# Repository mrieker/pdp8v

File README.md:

Vacuum tube implementation of PDP-8/V using a Raspberry PI for memory and I/O devices.
Webpage:  https://www.outerworldapps.com/pdp8v
Latest routed PCBs:
    https://www.outerworldapps.com/pdp8v/acl-2024-04-15.tgz
    https://www.outerworldapps.com/pdp8v/alu-2024-04-15.tgz
    https://www.outerworldapps.com/pdp8v/ma-2024-04-15.tgz
    https://www.outerworldapps.com/pdp8v/pc-2024-04-15.tgz
    https://www.outerworldapps.com/pdp8v/rpi-2024-04-15.tgz
    https://www.outerworldapps.com/pdp8v/seq-2024-04-15.tgz

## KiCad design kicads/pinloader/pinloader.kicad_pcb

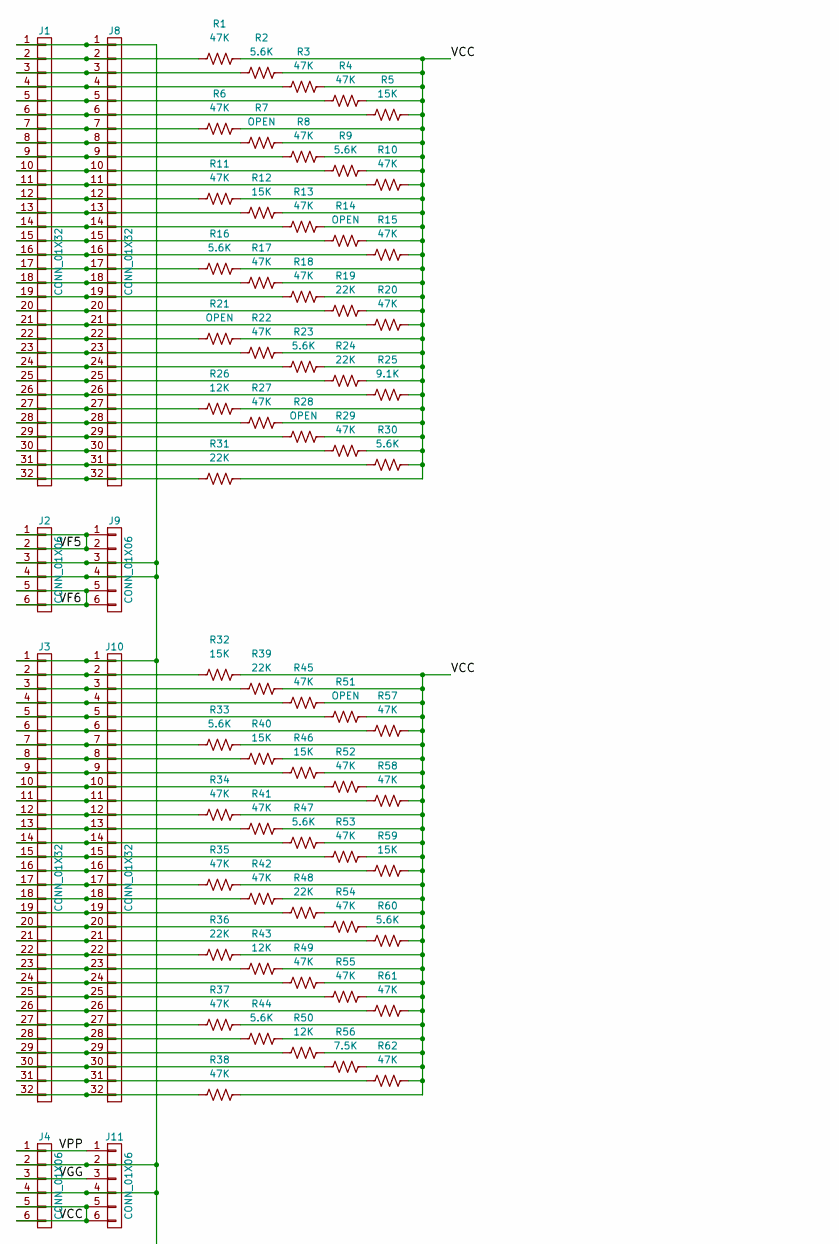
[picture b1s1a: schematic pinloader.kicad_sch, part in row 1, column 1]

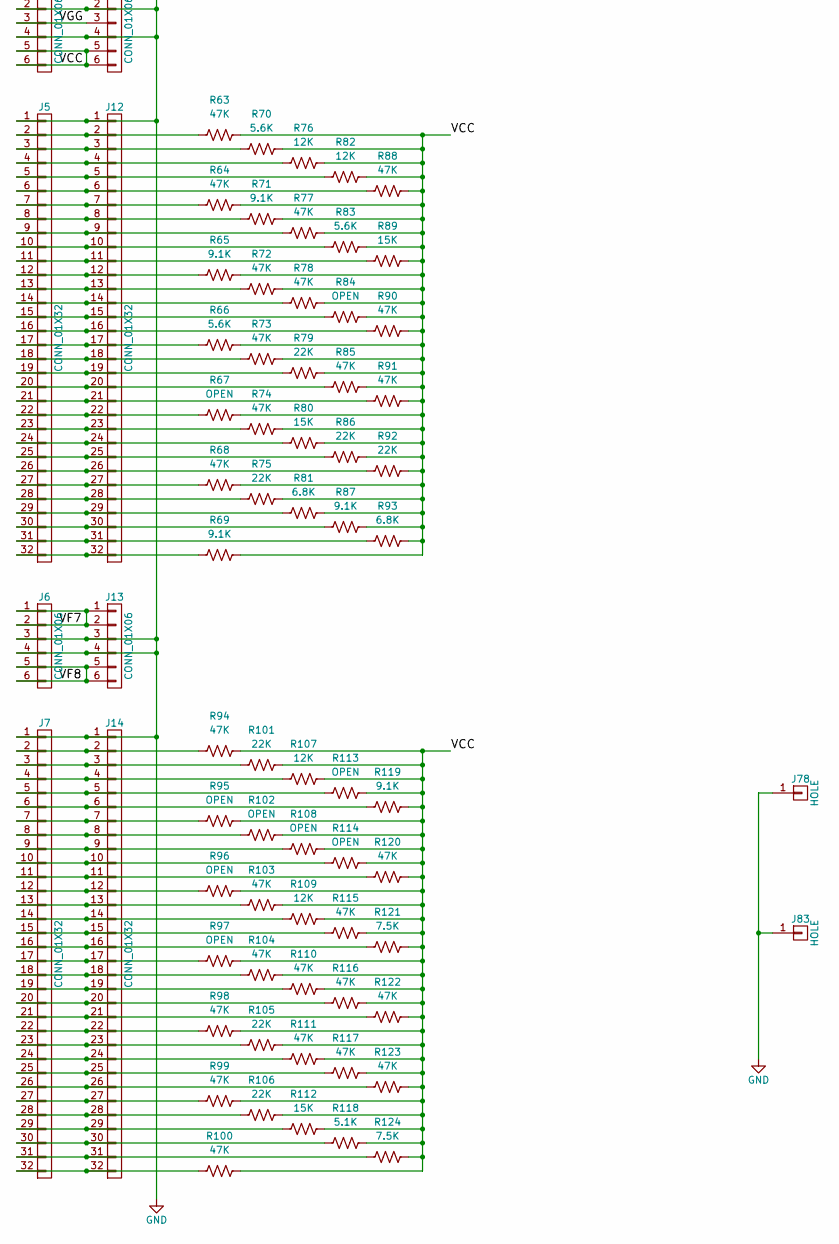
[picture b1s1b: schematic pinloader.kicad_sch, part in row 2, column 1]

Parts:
J1, J3, J5, J7, J8, J10, J12, J14: CONN_01X32; Pin_Header_Straight_1x32_Pitch2.54mm
J2, J4, J6, J9, J11, J13: CONN_01X06; Pin_Header_Straight_1x06_Pitch2.54mm
J78, J83: HOLE; 1pin
R1, R3, R4, R6, R8, R10, R11, R13, R15, R17, R18, R20, R22, R27, R29, R34, R35, R37, R38, R41, R42, R45, R49, R52, R53, R54, R55, R57, R58, R61, R62, R63, R64, R68, R72, R73, R74, R77, R78, R85, R88, R90, R91, R94, R98, R99, R100, R103, R104, R110, R111, R115, R116, R117, R120, R122, R123: 47K; R_Axial_DIN0207_L6.3mm_D2.5mm_P10.16mm_Horizontal
R2, R9, R16, R23, R30, R33, R44, R47, R60, R66, R70, R83: 5.6K; R_Axial_DIN0207_L6.3mm_D2.5mm_P10.16mm_Horizontal
R5, R12, R32, R40, R46, R59, R80, R89, R112: 15K; R_Axial_DIN0207_L6.3mm_D2.5mm_P10.16mm_Horizontal
R7, R14, R21, R28, R51, R67, R84, R95, R96, R97, R102, R108, R113, R114: OPEN; R_Axial_DIN0207_L6.3mm_D2.5mm_P10.16mm_Horizontal
R19, R24, R31, R36, R39, R48, R75, R79, R86, R92, R101, R105, R106: 22K; R_Axial_DIN0207_L6.3mm_D2.5mm_P10.16mm_Horizontal
R25, R65, R69, R71, R87, R119: 9.1K; R_Axial_DIN0207_L6.3mm_D2.5mm_P10.16mm_Horizontal
R26, R43, R50, R76, R82, R107, R109: 12K; R_Axial_DIN0207_L6.3mm_D2.5mm_P10.16mm_Horizontal
R56, R121, R124: 7.5K; R_Axial_DIN0207_L6.3mm_D2.5mm_P10.16mm_Horizontal
R81, R93: 6.8K; R_Axial_DIN0207_L6.3mm_D2.5mm_P10.16mm_Horizontal
R118: 5.1K; R_Axial_DIN0207_L6.3mm_D2.5mm_P10.16mm_Horizontal

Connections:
/VCC: J4.5, J4.6, J11.5, J11.6, R1.2, R2.2, R3.2, R4.2, R5.2, R6.2, R7.2, R8.2, R9.2, R10.2, R11.2, R12.2, R13.2, R14.2, R15.2, R16.2, R17.2, R18.2, R19.2, R20.2, R21.2, R22.2, R23.2, R24.2, R25.2, R26.2, R27.2, R28.2, R29.2, R30.2, R31.2, R32.2, R33.2, R34.2, R35.2, R36.2, R37.2, R38.2, R39.2, R40.2, R41.2, R42.2, R43.2, R44.2, R45.2, R46.2, R47.2, R48.2, R49.2, R50.2, R51.2, R52.2, R53.2, R54.2, R55.2, R56.2, R57.2, R58.2, R59.2, R60.2, R61.2, R62.2, R63.2, R64.2, R65.2, R66.2, R67.2, R68.2, R69.2, R70.2, R71.2, R72.2, R73.2, R74.2, R75.2, R76.2, R77.2, R78.2, R79.2, R80.2, R81.2, R82.2, R83.2, R84.2, R85.2, R86.2, R87.2, R88.2, R89.2, R90.2, R91.2, R92.2, R93.2, R94.2, R95.2, R96.2, R97.2, R98.2, R99.2, R100.2, R101.2, R102.2, R103.2, R104.2, R105.2, R106.2, R107.2, R108.2, R109.2, R110.2, R111.2, R112.2, R113.2, R114.2, R115.2, R116.2, R117.2, R118.2, R119.2, R120.2, R121.2, R122.2, R123.2, R124.2
/VF5: J2.1, J2.2, J9.1, J9.2
/VF6: J2.5, J2.6, J9.5, J9.6
/VF7: J6.1, J6.2, J13.1, J13.2
/VF8: J6.5, J6.6, J13.5, J13.6
/VGG: J4.3, J11.3
/VPP: J4.1, J11.1
GND: J1.1, J2.3, J2.4, J3.1, J4.2, J4.4, J5.1, J6.3, J6.4, J7.1, J8.1, J9.3, J9.4, J10.1, J11.2, J11.4, J12.1, J13.3, J13.4, J14.1, J78.1, J83.1
unnamed: J1.2, J8.2, R1.1
unnamed: J1.3, J8.3, R2.1
unnamed: J1.4, J8.4, R3.1
unnamed: J1.5, J8.5, R4.1
unnamed: J1.6, J8.6, R5.1
unnamed: J1.7, J8.7, R6.1
unnamed: J1.8, J8.8, R7.1
unnamed: J1.9, J8.9, R8.1
unnamed: J1.10, J8.10, R9.1
unnamed: J1.11, J8.11, R10.1
unnamed: J1.12, J8.12, R11.1
unnamed: J1.13, J8.13, R12.1
unnamed: J1.14, J8.14, R13.1
unnamed: J1.15, J8.15, R14.1
unnamed: J1.16, J8.16, R15.1
unnamed: J1.17, J8.17, R16.1
unnamed: J1.18, J8.18, R17.1
unnamed: J1.19, J8.19, R18.1
unnamed: J1.20, J8.20, R19.1
unnamed: J1.21, J8.21, R20.1
unnamed: J1.22, J8.22, R21.1
unnamed: J1.23, J8.23, R22.1
unnamed: J1.24, J8.24, R23.1
unnamed: J1.25, J8.25, R24.1
unnamed: J1.26, J8.26, R25.1
unnamed: J1.27, J8.27, R26.1
unnamed: J1.28, J8.28, R27.1
unnamed: J1.29, J8.29, R28.1
unnamed: J1.30, J8.30, R29.1
unnamed: J1.31, J8.31, R30.1
unnamed: J1.32, J8.32, R31.1
unnamed: J3.2, J10.2, R32.1
unnamed: J3.3, J10.3, R39.1
unnamed: J3.4, J10.4, R45.1
unnamed: J3.5, J10.5, R51.1
unnamed: J3.6, J10.6, R57.1
unnamed: J3.7, J10.7, R33.1
unnamed: J3.8, J10.8, R40.1
unnamed: J3.9, J10.9, R46.1
unnamed: J3.10, J10.10, R52.1
unnamed: J3.11, J10.11, R58.1
unnamed: J3.12, J10.12, R34.1
unnamed: J3.13, J10.13, R41.1
unnamed: J3.14, J10.14, R47.1
unnamed: J3.15, J10.15, R53.1
unnamed: J3.16, J10.16, R59.1
unnamed: J3.17, J10.17, R35.1
unnamed: J3.18, J10.18, R42.1
unnamed: J3.19, J10.19, R48.1
unnamed: J3.20, J10.20, R54.1
unnamed: J3.21, J10.21, R60.1
unnamed: J3.22, J10.22, R36.1
unnamed: J3.23, J10.23, R43.1
unnamed: J3.24, J10.24, R49.1
unnamed: J3.25, J10.25, R55.1
unnamed: J3.26, J10.26, R61.1
unnamed: J3.27, J10.27, R37.1
unnamed: J3.28, J10.28, R44.1
unnamed: J3.29, J10.29, R50.1
unnamed: J3.30, J10.30, R56.1
unnamed: J3.31, J10.31, R62.1
unnamed: J3.32, J10.32, R38.1
unnamed: J5.2, J12.2, R63.1
unnamed: J5.3, J12.3, R70.1
unnamed: J5.4, J12.4, R76.1
unnamed: J5.5, J12.5, R82.1
unnamed: J5.6, J12.6, R88.1
unnamed: J5.7, J12.7, R64.1
unnamed: J5.8, J12.8, R71.1
unnamed: J5.9, J12.9, R77.1
unnamed: J5.10, J12.10, R83.1
unnamed: J5.11, J12.11, R89.1
unnamed: J5.12, J12.12, R65.1
unnamed: J5.13, J12.13, R72.1
unnamed: J5.14, J12.14, R78.1
unnamed: J5.15, J12.15, R84.1
unnamed: J5.16, J12.16, R90.1
unnamed: J5.17, J12.17, R66.1
unnamed: J5.18, J12.18, R73.1
unnamed: J5.19, J12.19, R79.1
unnamed: J5.20, J12.20, R85.1
unnamed: J5.21, J12.21, R91.1
unnamed: J5.22, J12.22, R67.1
unnamed: J5.23, J12.23, R74.1
unnamed: J5.24, J12.24, R80.1
unnamed: J5.25, J12.25, R86.1
unnamed: J5.26, J12.26, R92.1
unnamed: J5.27, J12.27, R68.1
unnamed: J5.28, J12.28, R75.1
unnamed: J5.29, J12.29, R81.1
unnamed: J5.30, J12.30, R87.1
unnamed: J5.31, J12.31, R93.1
unnamed: J5.32, J12.32, R69.1
unnamed: J7.2, J14.2, R94.1
unnamed: J7.3, J14.3, R101.1
unnamed: J7.4, J14.4, R107.1
unnamed: J7.5, J14.5, R113.1
unnamed: J7.6, J14.6, R119.1
unnamed: J7.7, J14.7, R95.1
unnamed: J7.8, J14.8, R102.1
unnamed: J7.9, J14.9, R108.1
unnamed: J7.10, J14.10, R114.1
unnamed: J7.11, J14.11, R120.1
unnamed: J7.12, J14.12, R96.1
unnamed: J7.13, J14.13, R103.1
unnamed: J7.14, J14.14, R109.1
unnamed: J7.15, J14.15, R115.1
unnamed: J7.16, J14.16, R121.1
unnamed: J7.17, J14.17, R97.1
unnamed: J7.18, J14.18, R104.1
unnamed: J7.19, J14.19, R110.1
unnamed: J7.20, J14.20, R116.1
unnamed: J7.21, J14.21, R122.1
unnamed: J7.22, J14.22, R98.1
unnamed: J7.23, J14.23, R105.1
unnamed: J7.24, J14.24, R111.1
unnamed: J7.25, J14.25, R117.1
unnamed: J7.26, J14.26, R123.1
unnamed: J7.27, J14.27, R99.1
unnamed: J7.28, J14.28, R106.1
unnamed: J7.29, J14.29, R112.1
unnamed: J7.30, J14.30, R118.1
unnamed: J7.31, J14.31, R124.1
unnamed: J7.32, J14.32, R100.1

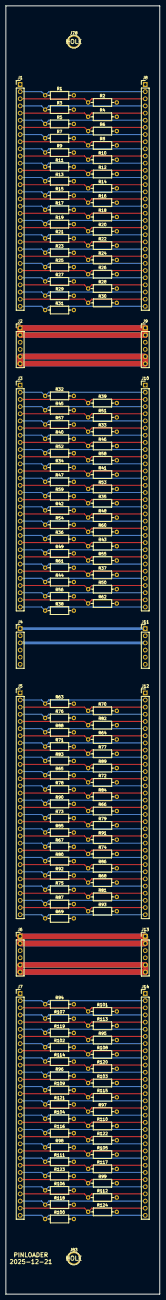
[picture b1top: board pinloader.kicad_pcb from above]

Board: 4 copper layers, 54.6 x 457.2 mm, 140 parts (0 on the bottom side), 132 nets.

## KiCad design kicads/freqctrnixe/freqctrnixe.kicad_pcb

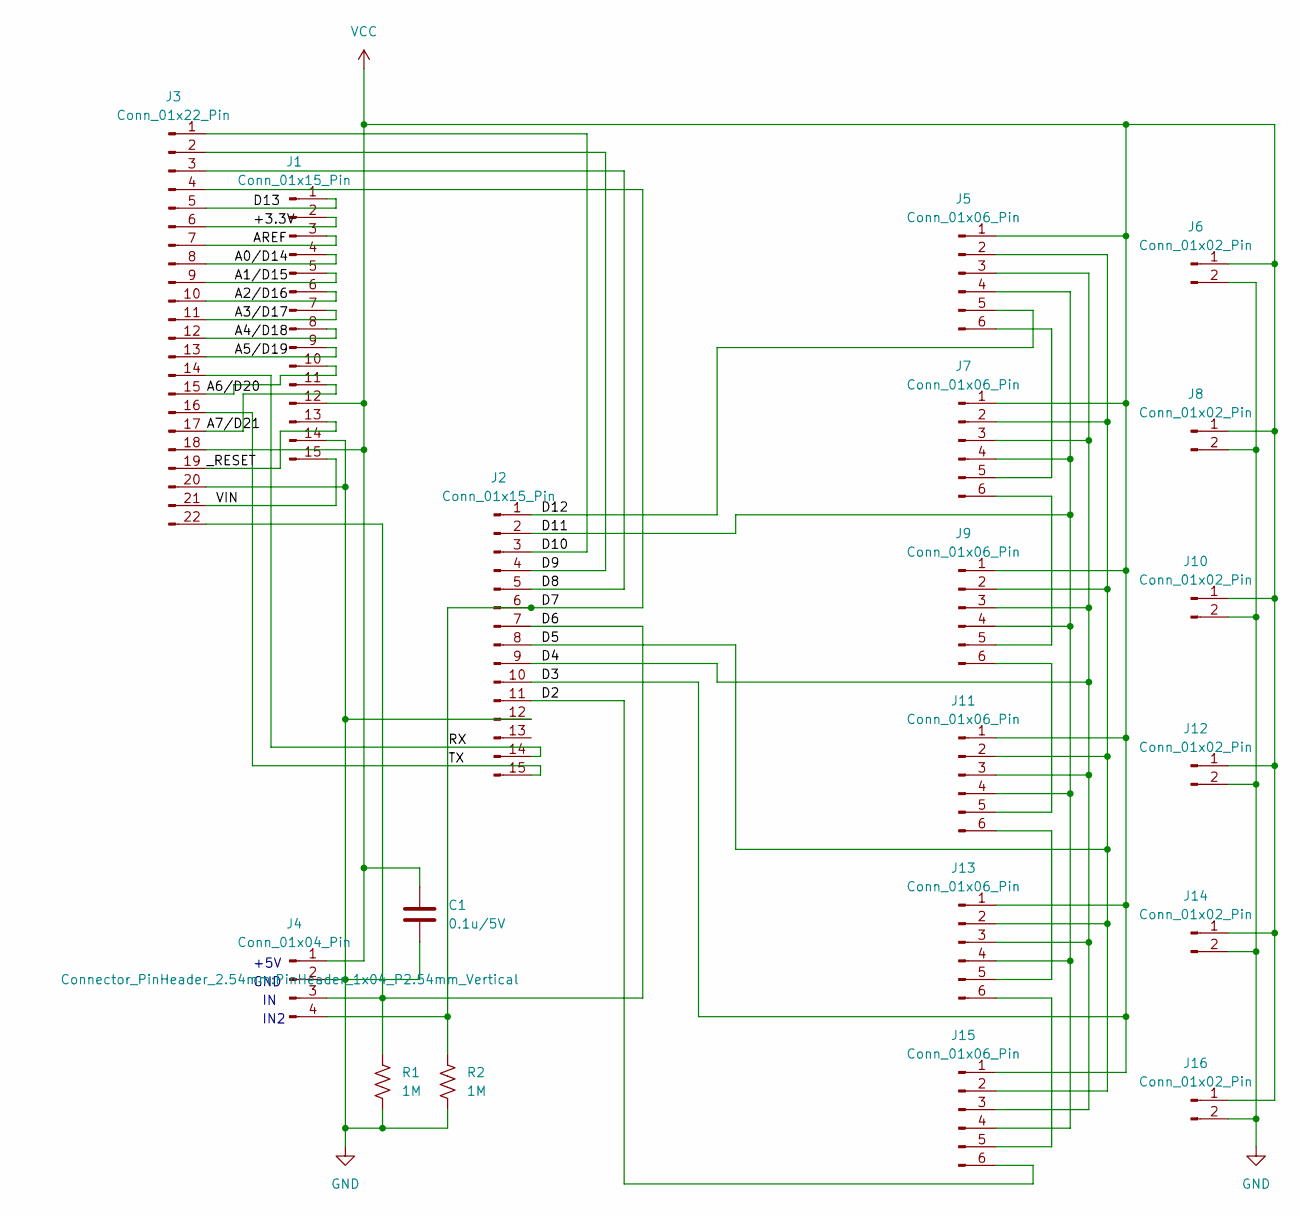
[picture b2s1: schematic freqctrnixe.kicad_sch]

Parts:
C1: 0.1u/5V; C_Axial_L3.8mm_D2.6mm_P7.50mm_Horizontal
J1, J2: Conn_01x15_Pin; PinHeader_1x15_P2.54mm_Vertical
J3: Conn_01x22_Pin; PinHeader_1x22_P2.54mm_Vertical
J4: Conn_01x04_Pin; PinHeader_1x04_P2.54mm_Vertical
J5, J7, J9, J11, J13, J15: Conn_01x06_Pin; PinHeader_1x06_P2.54mm_Vertical
J6, J8, J10, J12, J14, J16: Conn_01x02_Pin; PinHeader_1x02_P2.54mm_Vertical
R1, R2: 1M; R_Axial_DIN0204_L3.6mm_D1.6mm_P7.62mm_Horizontal

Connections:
/+3.3V: J1.2, J3.6
/A0/D14: J1.4, J3.8
/A1/D15: J1.5, J3.9
/A2/D16: J1.6, J3.10
/A3/D17: J1.7, J3.11
/A4/D18: J1.8, J3.12
/A5/D19: J1.9, J3.13
/A6/D20: J1.10, J3.15
/A7/D21: J1.11, J3.17
/AREF: J1.3, J3.7
/D2: J2.11, J15.6
/D4: J2.9, J5.3, J7.3, J9.3, J11.3, J13.3, J15.3
/D5: J2.8, J5.2, J7.2, J9.2, J11.2, J13.2, J15.2
/D6: J2.7, J3.22, J4.3, R1.1
/D8: J2.5, J3.3
/D9: J2.4, J3.2
/D10: J2.3, J3.1
/D11: J2.2, J5.4, J7.4, J9.4, J11.4, J13.4, J15.4
/D12: J2.1, J5.5
/D13: J1.1, J3.5
/VIN: J1.15, J3.21
/_RESET: J1.13, J3.19
GND: C1.2, J1.14, J2.12, J3.20, J4.2, J6.2, J8.2, J10.2, J12.2, J14.2, J16.2, R1.2, R2.2
unnamed: J5.6, J7.5
unnamed: J7.6, J9.5
unnamed: J9.6, J11.5
unnamed: J11.6, J13.5
unnamed: J13.6, J15.5
VCC: C1.1, J1.12, J2.10, J3.18, J4.1, J5.1, J6.1, J7.1, J8.1, J9.1, J10.1, J11.1, J12.1, J13.1, J14.1, J15.1, J16.1

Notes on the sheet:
+5V
IN2
GND

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
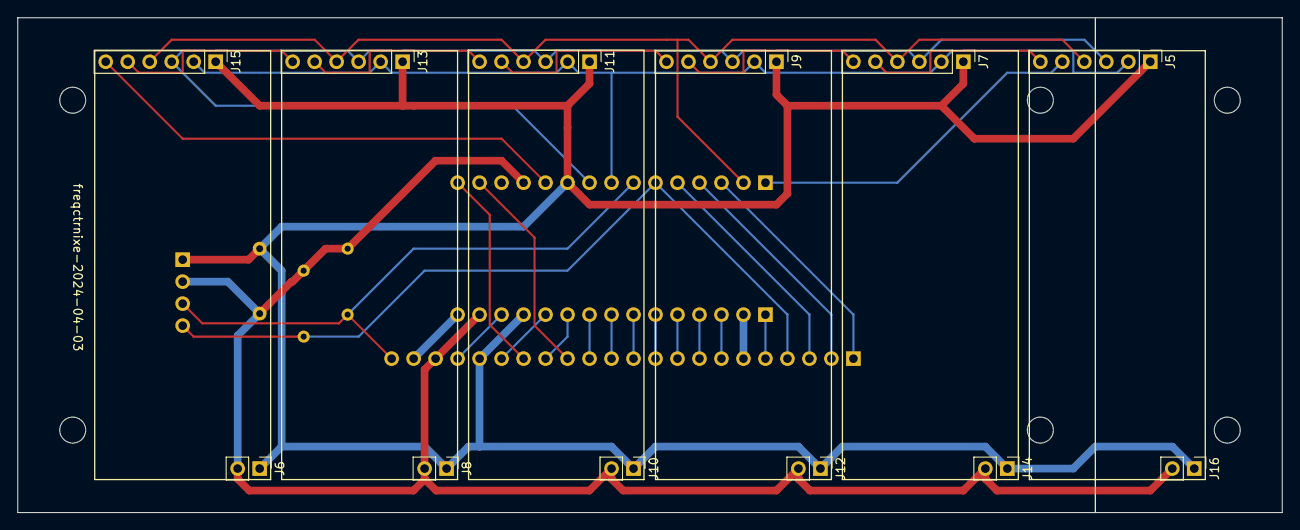
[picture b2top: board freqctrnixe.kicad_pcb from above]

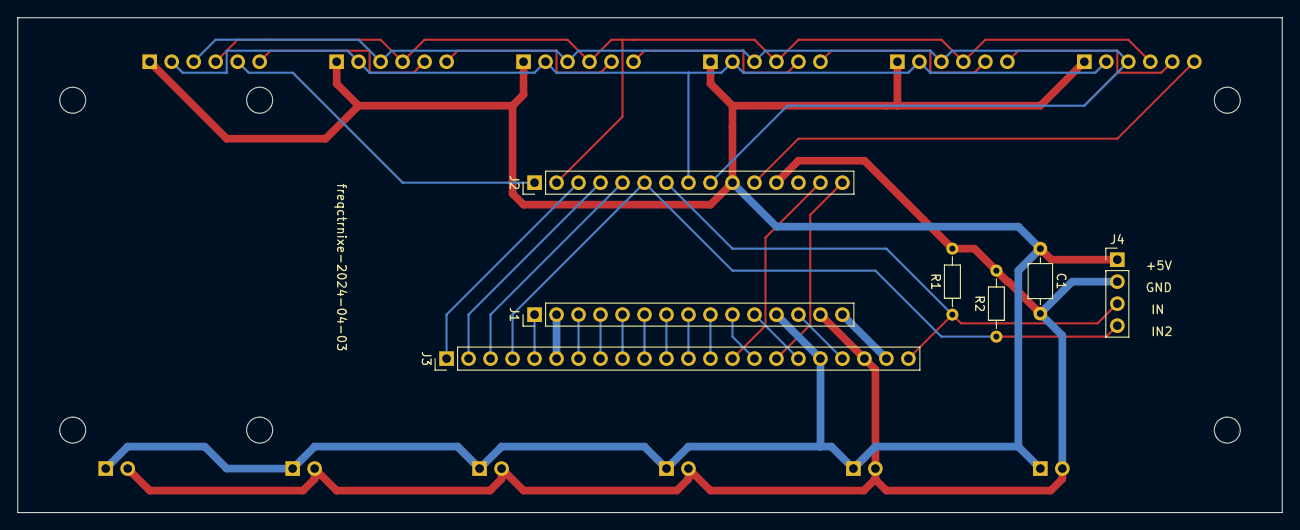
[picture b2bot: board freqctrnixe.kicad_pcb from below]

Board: 2 copper layers, 146.1 x 57.1 mm, 19 parts (7 on the bottom side), 32 nets.

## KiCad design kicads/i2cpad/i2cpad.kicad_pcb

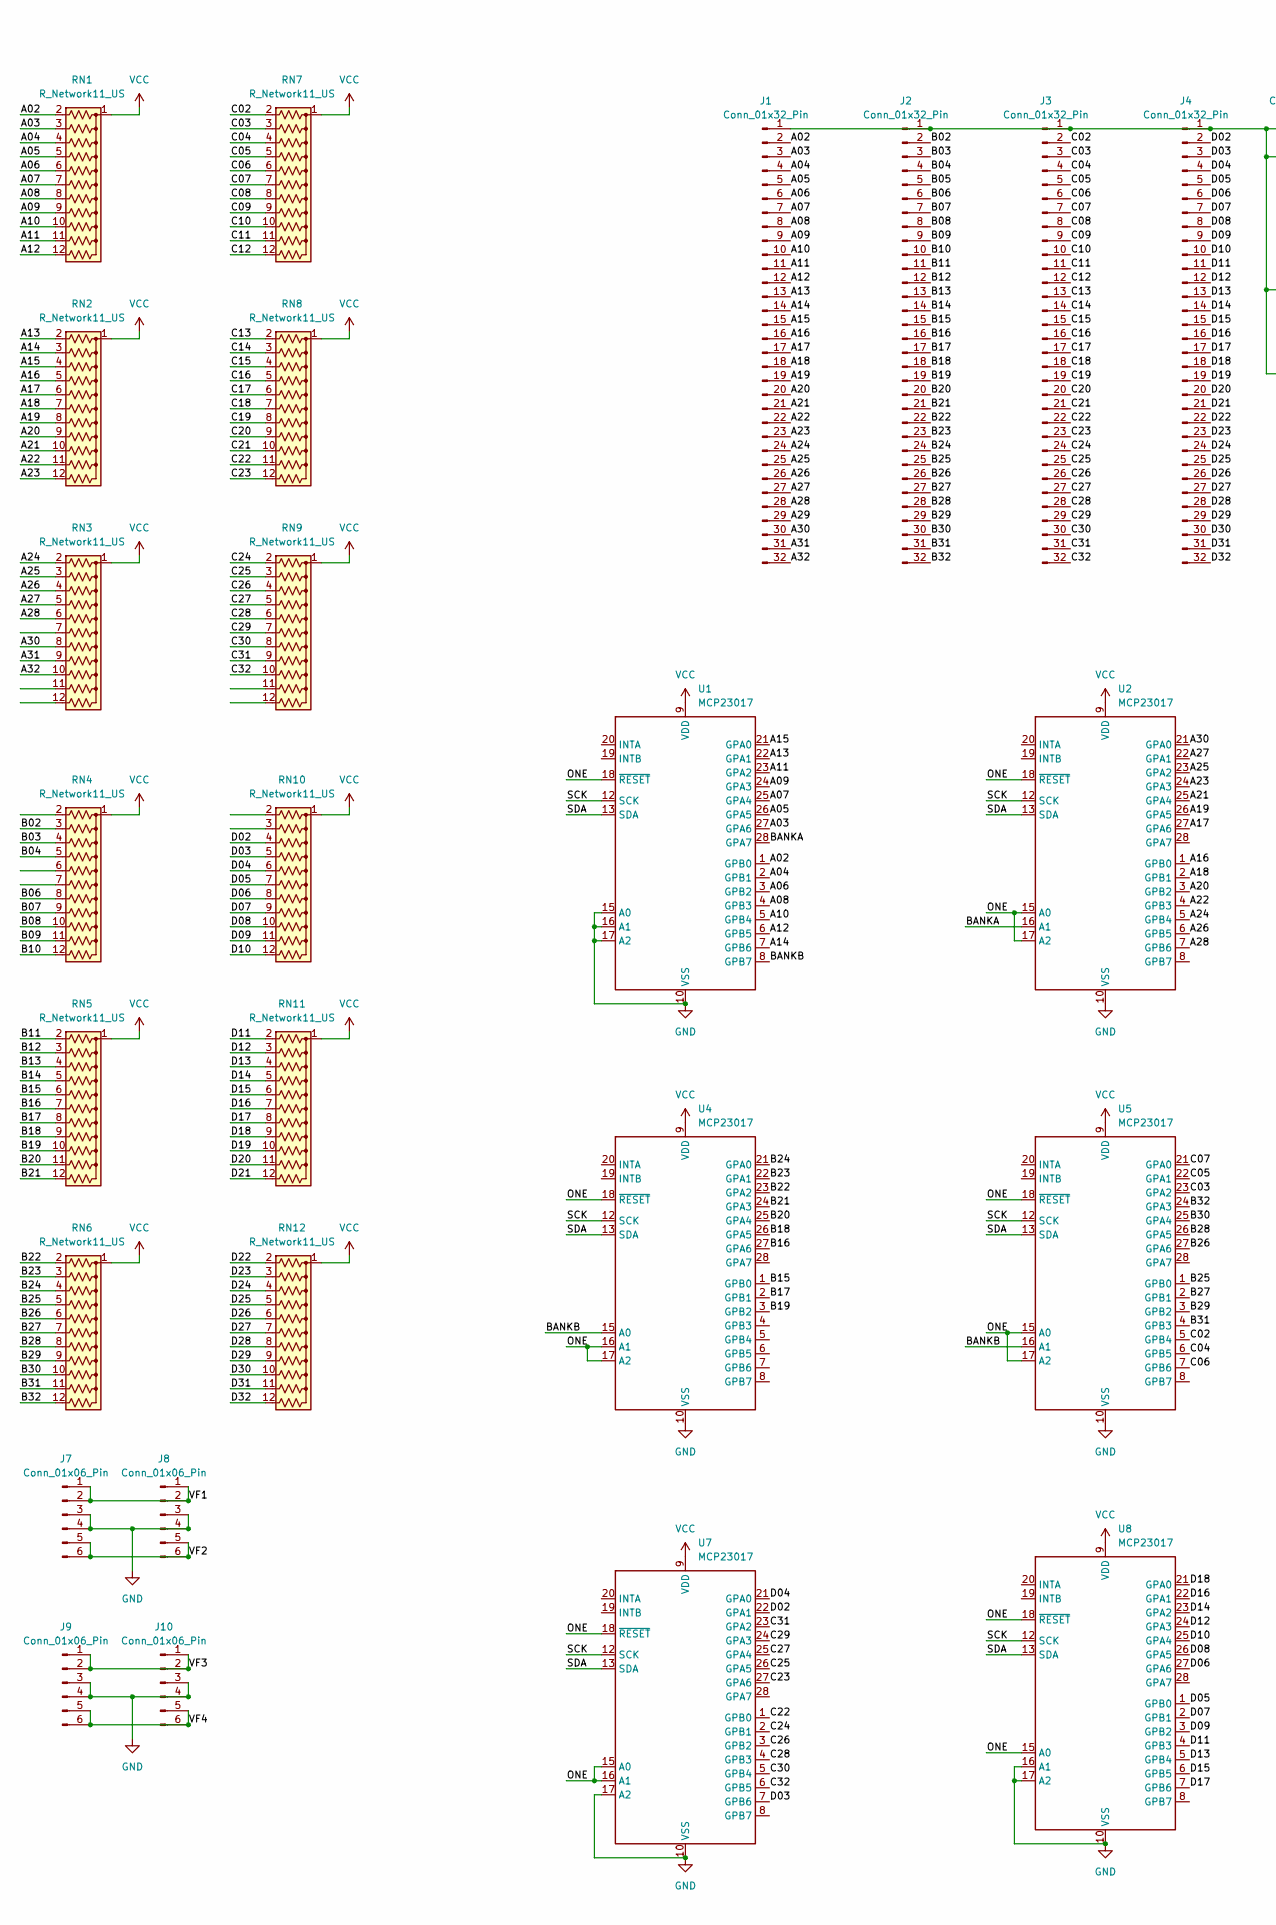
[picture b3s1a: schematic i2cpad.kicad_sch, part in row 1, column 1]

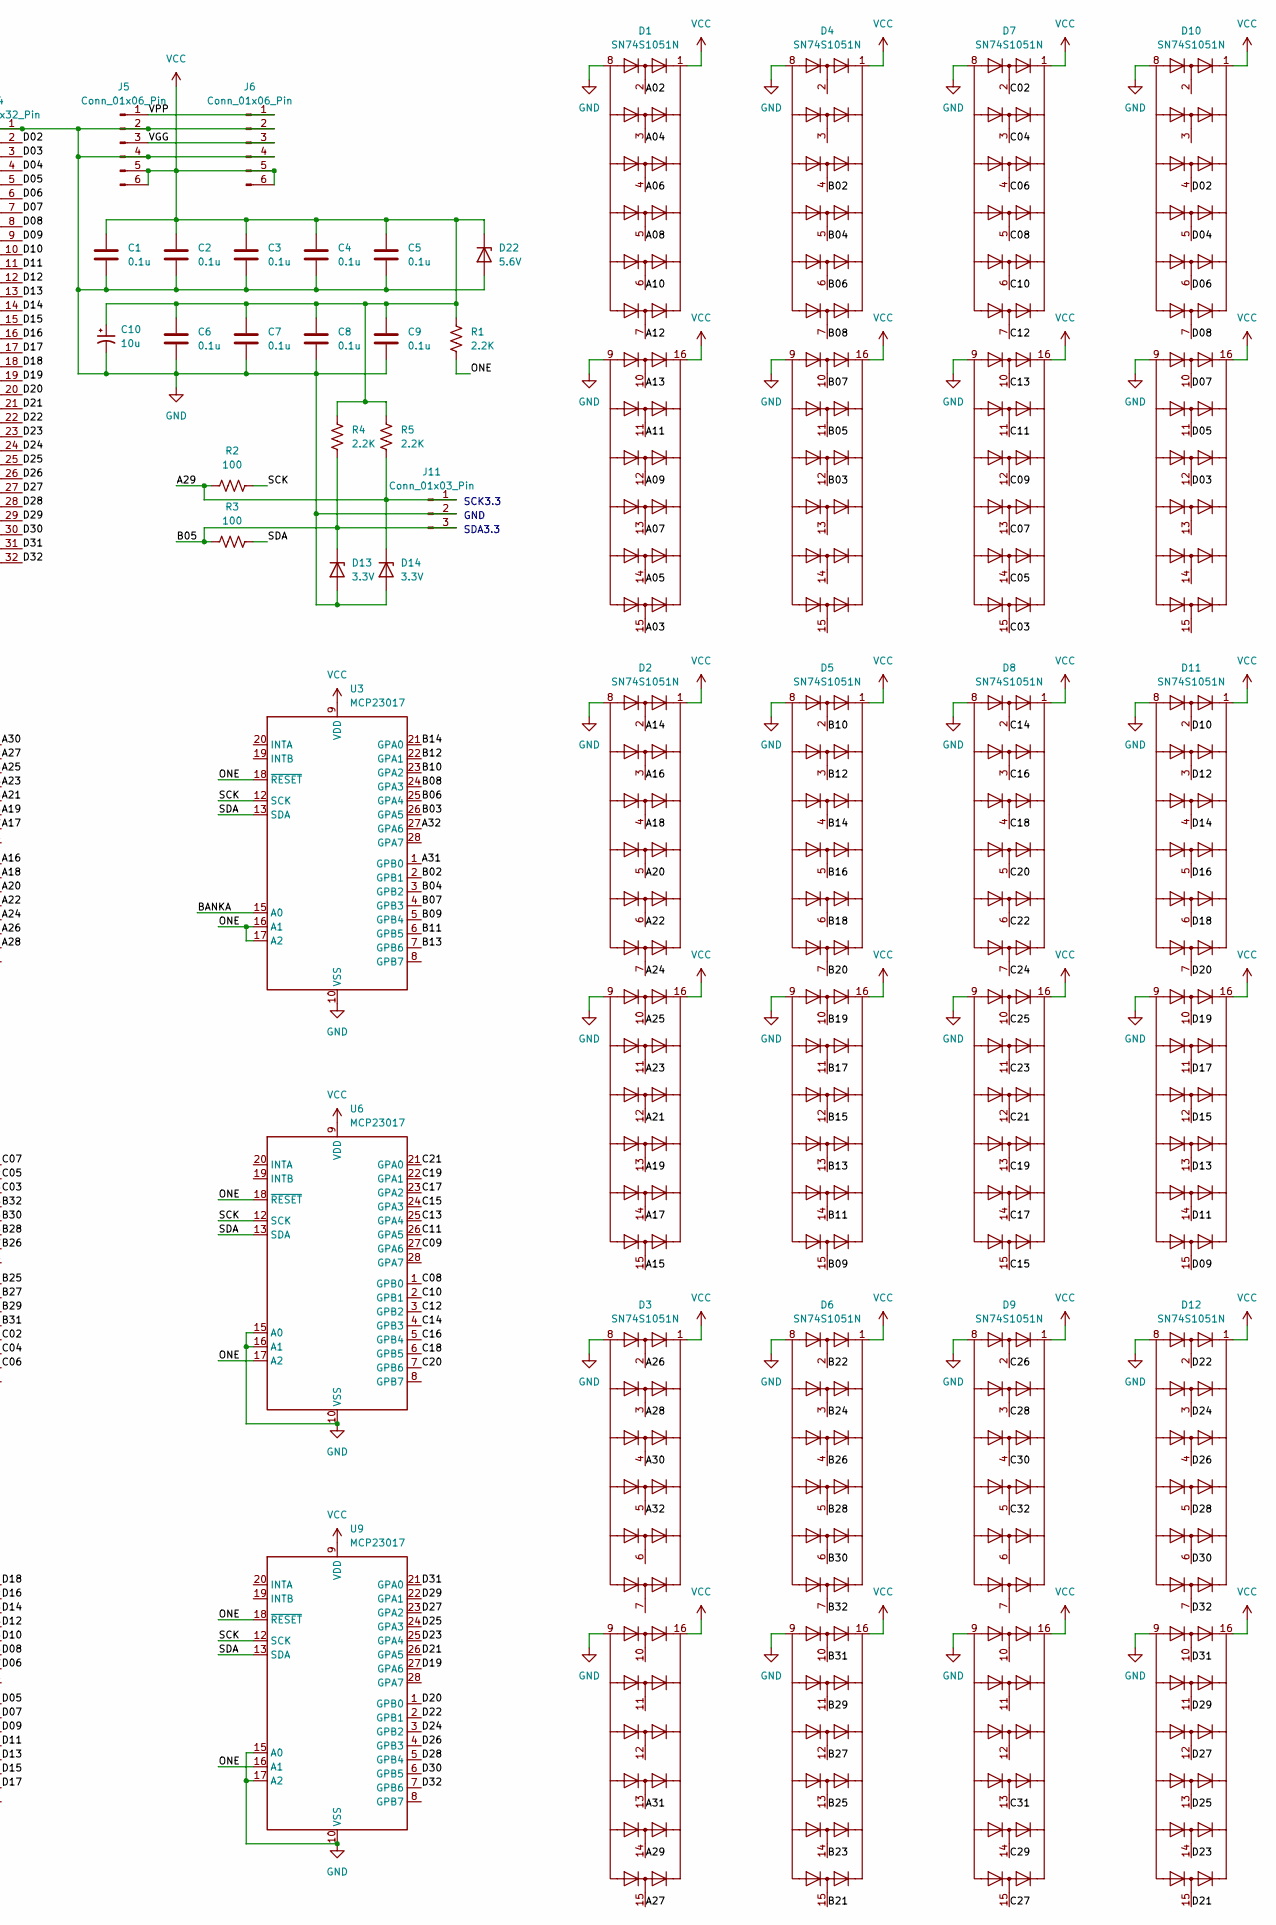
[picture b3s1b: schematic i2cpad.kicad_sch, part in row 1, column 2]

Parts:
C1, C2, C3, C4, C5, C6, C7, C8, C9: 0.1u; C_Axial_L5.1mm_D3.1mm_P7.50mm_Horizontal
C10: 10u; CP_Axial_L10.0mm_D4.5mm_P15.00mm_Horizontal
D1, D2, D3, D4, D5, D6, D7, D8, D9, D10, D11, D12: SN74S1051N; DIP-16_W7.62mm_LongPads
D13, D14: 3.3V; D_T-1_P10.16mm_Horizontal
D22: 5.6V; D_T-1_P10.16mm_Horizontal
J1, J2, J3, J4: Conn_01x32_Pin; PinHeader_1x32_P2.54mm_Vertical
J5, J6, J7, J8, J9, J10: Conn_01x06_Pin; PinHeader_1x06_P2.54mm_Vertical
J11: Conn_01x03_Pin; PinHeader_1x03_P2.54mm_Vertical
R1, R4, R5: 2.2K; R_Axial_DIN0204_L3.6mm_D1.6mm_P7.62mm_Horizontal
R2, R3: 100; R_Axial_DIN0204_L3.6mm_D1.6mm_P7.62mm_Horizontal
RN1, RN2, RN3, RN4, RN5, RN6, RN7, RN8, RN9, RN10, RN11, RN12: R_Network11_US; R_Array_SIP12
U1, U2, U3, U4, U5, U6, U7, U8, U9: MCP23017; DIP-28_W7.62mm_LongPads

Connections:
/A02: D1.2 (X2), J1.2, RN1.2 (R1), U1.1 (GPB0)
/A03: D1.15 (X15), J1.3, RN1.3 (R2), U1.27 (GPA6)
/A04: D1.3 (X3), J1.4, RN1.4 (R3), U1.2 (GPB1)
/A05: D1.14 (X14), J1.5, RN1.5 (R4), U1.26 (GPA5)
/A06: D1.4 (X4), J1.6, RN1.6 (R5), U1.3 (GPB2)
/A07: D1.13 (X13), J1.7, RN1.7 (R6), U1.25 (GPA4)
/A08: D1.5 (X5), J1.8, RN1.8 (R7), U1.4 (GPB3)
/A09: D1.12 (X12), J1.9, RN1.9 (R8), U1.24 (GPA3)
/A10: D1.6 (X6), J1.10, RN1.10 (R9), U1.5 (GPB4)
/A11: D1.11 (X11), J1.11, RN1.11 (R10), U1.23 (GPA2)
/A12: D1.7 (X7), J1.12, RN1.12 (R11), U1.6 (GPB5)
/A13: D1.10 (X10), J1.13, RN2.2 (R1), U1.22 (GPA1)
/A14: D2.2 (X2), J1.14, RN2.3 (R2), U1.7 (GPB6)
/A15: D2.15 (X15), J1.15, RN2.4 (R3), U1.21 (GPA0)
/A16: D2.3 (X3), J1.16, RN2.5 (R4), U2.1 (GPB0)
/A17: D2.14 (X14), J1.17, RN2.6 (R5), U2.27 (GPA6)
/A18: D2.4 (X4), J1.18, RN2.7 (R6), U2.2 (GPB1)
/A19: D2.13 (X13), J1.19, RN2.8 (R7), U2.26 (GPA5)
/A20: D2.5 (X5), J1.20, RN2.9 (R8), U2.3 (GPB2)
/A21: D2.12 (X12), J1.21, RN2.10 (R9), U2.25 (GPA4)
/A22: D2.6 (X6), J1.22, RN2.11 (R10), U2.4 (GPB3)
/A23: D2.11 (X11), J1.23, RN2.12 (R11), U2.24 (GPA3)
/A24: D2.7 (X7), J1.24, RN3.2 (R1), U2.5 (GPB4)
/A25: D2.10 (X10), J1.25, RN3.3 (R2), U2.23 (GPA2)
/A26: D3.2 (X2), J1.26, RN3.4 (R3), U2.6 (GPB5)
/A27: D3.15 (X15), J1.27, RN3.5 (R4), U2.22 (GPA1)
/A28: D3.3 (X3), J1.28, RN3.6 (R5), U2.7 (GPB6)
/A29: D3.14 (X14), D14.1 (K), J1.29, J11.1, R2.1, R5.2
/A30: D3.4 (X4), J1.30, RN3.8 (R7), U2.21 (GPA0)
/A31: D3.13 (X13), J1.31, RN3.9 (R8), U3.1 (GPB0)
/A32: D3.5 (X5), J1.32, RN3.10 (R9), U3.27 (GPA6)
/B02: D4.4 (X4), J2.2, RN4.3 (R2), U3.2 (GPB1)
/B03: D4.12 (X12), J2.3, RN4.4 (R3), U3.26 (GPA5)
/B04: D4.5 (X5), J2.4, RN4.5 (R4), U3.3 (GPB2)
/B05: D4.11 (X11), D13.1 (K), J2.5, J11.3, R3.1, R4.2
/B06: D4.6 (X6), J2.6, RN4.8 (R7), U3.25 (GPA4)
/B07: D4.10 (X10), J2.7, RN4.9 (R8), U3.4 (GPB3)
/B08: D4.7 (X7), J2.8, RN4.10 (R9), U3.24 (GPA3)
/B09: D5.15 (X15), J2.9, RN4.11 (R10), U3.5 (GPB4)
/B10: D5.2 (X2), J2.10, RN4.12 (R11), U3.23 (GPA2)
/B11: D5.14 (X14), J2.11, RN5.2 (R1), U3.6 (GPB5)
/B12: D5.3 (X3), J2.12, RN5.3 (R2), U3.22 (GPA1)
/B13: D5.13 (X13), J2.13, RN5.4 (R3), U3.7 (GPB6)
/B14: D5.4 (X4), J2.14, RN5.5 (R4), U3.21 (GPA0)
/B15: D5.12 (X12), J2.15, RN5.6 (R5), U4.1 (GPB0)
/B16: D5.5 (X5), J2.16, RN5.7 (R6), U4.27 (GPA6)
/B17: D5.11 (X11), J2.17, RN5.8 (R7), U4.2 (GPB1)
/B18: D5.6 (X6), J2.18, RN5.9 (R8), U4.26 (GPA5)
/B19: D5.10 (X10), J2.19, RN5.10 (R9), U4.3 (GPB2)
/B20: D5.7 (X7), J2.20, RN5.11 (R10), U4.25 (GPA4)
/B21: D6.15 (X15), J2.21, RN5.12 (R11), U4.24 (GPA3)
/B22: D6.2 (X2), J2.22, RN6.2 (R1), U4.23 (GPA2)
/B23: D6.14 (X14), J2.23, RN6.3 (R2), U4.22 (GPA1)
/B24: D6.3 (X3), J2.24, RN6.4 (R3), U4.21 (GPA0)
/B25: D6.13 (X13), J2.25, RN6.5 (R4), U5.1 (GPB0)
/B26: D6.4 (X4), J2.26, RN6.6 (R5), U5.27 (GPA6)
/B27: D6.12 (X12), J2.27, RN6.7 (R6), U5.2 (GPB1)
/B28: D6.5 (X5), J2.28, RN6.8 (R7), U5.26 (GPA5)
/B29: D6.11 (X11), J2.29, RN6.9 (R8), U5.3 (GPB2)
/B30: D6.6 (X6), J2.30, RN6.10 (R9), U5.25 (GPA4)
/B31: D6.10 (X10), J2.31, RN6.11 (R10), U5.4 (GPB3)
/B32: D6.7 (X7), J2.32, RN6.12 (R11), U5.24 (GPA3)
/BANKA: U1.28 (GPA7), U2.16 (A1), U3.15 (A0)
/BANKB: U1.8 (GPB7), U4.15 (A0), U5.16 (A1)
/C02: D7.2 (X2), J3.2, RN7.2 (R1), U5.5 (GPB4)
/C03: D7.15 (X15), J3.3, RN7.3 (R2), U5.23 (GPA2)
/C04: D7.3 (X3), J3.4, RN7.4 (R3), U5.6 (GPB5)
/C05: D7.14 (X14), J3.5, RN7.5 (R4), U5.22 (GPA1)
/C06: D7.4 (X4), J3.6, RN7.6 (R5), U5.7 (GPB6)
/C07: D7.13 (X13), J3.7, RN7.7 (R6), U5.21 (GPA0)
/C08: D7.5 (X5), J3.8, RN7.8 (R7), U6.1 (GPB0)
/C09: D7.12 (X12), J3.9, RN7.9 (R8), U6.27 (GPA6)
/C10: D7.6 (X6), J3.10, RN7.10 (R9), U6.2 (GPB1)
/C11: D7.11 (X11), J3.11, RN7.11 (R10), U6.26 (GPA5)
/C12: D7.7 (X7), J3.12, RN7.12 (R11), U6.3 (GPB2)
/C13: D7.10 (X10), J3.13, RN8.2 (R1), U6.25 (GPA4)
/C14: D8.2 (X2), J3.14, RN8.3 (R2), U6.4 (GPB3)
/C15: D8.15 (X15), J3.15, RN8.4 (R3), U6.24 (GPA3)
/C16: D8.3 (X3), J3.16, RN8.5 (R4), U6.5 (GPB4)
/C17: D8.14 (X14), J3.17, RN8.6 (R5), U6.23 (GPA2)
/C18: D8.4 (X4), J3.18, RN8.7 (R6), U6.6 (GPB5)
/C19: D8.13 (X13), J3.19, RN8.8 (R7), U6.22 (GPA1)
/C20: D8.5 (X5), J3.20, RN8.9 (R8), U6.7 (GPB6)
/C21: D8.12 (X12), J3.21, RN8.10 (R9), U6.21 (GPA0)
/C22: D8.6 (X6), J3.22, RN8.11 (R10), U7.1 (GPB0)
/C23: D8.11 (X11), J3.23, RN8.12 (R11), U7.27 (GPA6)
/C24: D8.7 (X7), J3.24, RN9.2 (R1), U7.2 (GPB1)
/C25: D8.10 (X10), J3.25, RN9.3 (R2), U7.26 (GPA5)
/C26: D9.2 (X2), J3.26, RN9.4 (R3), U7.3 (GPB2)
/C27: D9.15 (X15), J3.27, RN9.5 (R4), U7.25 (GPA4)
/C28: D9.3 (X3), J3.28, RN9.6 (R5), U7.4 (GPB3)
/C29: D9.14 (X14), J3.29, RN9.7 (R6), U7.24 (GPA3)
/C30: D9.4 (X4), J3.30, RN9.8 (R7), U7.5 (GPB4)
/C31: D9.13 (X13), J3.31, RN9.9 (R8), U7.23 (GPA2)
/C32: D9.5 (X5), J3.32, RN9.10 (R9), U7.6 (GPB5)
/D02: D10.4 (X4), J4.2, RN10.4 (R3), U7.22 (GPA1)
/D03: D10.12 (X12), J4.3, RN10.5 (R4), U7.7 (GPB6)
/D04: D10.5 (X5), J4.4, RN10.6 (R5), U7.21 (GPA0)
/D05: D10.11 (X11), J4.5, RN10.7 (R6), U8.1 (GPB0)
/D06: D10.6 (X6), J4.6, RN10.8 (R7), U8.27 (GPA6)
/D07: D10.10 (X10), J4.7, RN10.9 (R8), U8.2 (GPB1)
/D08: D10.7 (X7), J4.8, RN10.10 (R9), U8.26 (GPA5)
/D09: D11.15 (X15), J4.9, RN10.11 (R10), U8.3 (GPB2)
/D10: D11.2 (X2), J4.10, RN10.12 (R11), U8.25 (GPA4)
/D11: D11.14 (X14), J4.11, RN11.2 (R1), U8.4 (GPB3)
/D12: D11.3 (X3), J4.12, RN11.3 (R2), U8.24 (GPA3)
/D13: D11.13 (X13), J4.13, RN11.4 (R3), U8.5 (GPB4)
/D14: D11.4 (X4), J4.14, RN11.5 (R4), U8.23 (GPA2)
/D15: D11.12 (X12), J4.15, RN11.6 (R5), U8.6 (GPB5)
/D16: D11.5 (X5), J4.16, RN11.7 (R6), U8.22 (GPA1)
/D17: D11.11 (X11), J4.17, RN11.8 (R7), U8.7 (GPB6)
/D18: D11.6 (X6), J4.18, RN11.9 (R8), U8.21 (GPA0)
/D19: D11.10 (X10), J4.19, RN11.10 (R9), U9.27 (GPA6)
/D20: D11.7 (X7), J4.20, RN11.11 (R10), U9.1 (GPB0)
/D21: D12.15 (X15), J4.21, RN11.12 (R11), U9.26 (GPA5)
/D22: D12.2 (X2), J4.22, RN12.2 (R1), U9.2 (GPB1)
/D23: D12.14 (X14), J4.23, RN12.3 (R2), U9.25 (GPA4)
/D24: D12.3 (X3), J4.24, RN12.4 (R3), U9.3 (GPB2)
/D25: D12.13 (X13), J4.25, RN12.5 (R4), U9.24 (GPA3)
/D26: D12.4 (X4), J4.26, RN12.6 (R5), U9.4 (GPB3)
/D27: D12.12 (X12), J4.27, RN12.7 (R6), U9.23 (GPA2)
/D28: D12.5 (X5), J4.28, RN12.8 (R7), U9.5 (GPB4)
/D29: D12.11 (X11), J4.29, RN12.9 (R8), U9.22 (GPA1)
/D30: D12.6 (X6), J4.30, RN12.10 (R9), U9.6 (GPB5)
/D31: D12.10 (X10), J4.31, RN12.11 (R10), U9.21 (GPA0)
/D32: D12.7 (X7), J4.32, RN12.12 (R11), U9.7 (GPB6)
/ONE: R1.2, U1.18 (~RESET), U2.15 (A0), U2.17 (A2), U2.18 (~RESET), U3.16 (A1), U3.17 (A2), U3.18 (~RESET), U4.16 (A1), U4.17 (A2), U4.18 (~RESET), U5.15 (A0), U5.17 (A2), U5.18 (~RESET), U6.17 (A2), U6.18 (~RESET), U7.15 (A0), U7.16 (A1), U7.18 (~RESET), U8.15 (A0), U8.18 (~RESET), U9.16 (A1), U9.18 (~RESET)
/SCK: R2.2, U1.12 (SCK), U2.12 (SCK), U3.12 (SCK), U4.12 (SCK), U5.12 (SCK), U6.12 (SCK), U7.12 (SCK), U8.12 (SCK), U9.12 (SCK)
/SDA: R3.2, U1.13 (SDA), U2.13 (SDA), U3.13 (SDA), U4.13 (SDA), U5.13 (SDA), U6.13 (SDA), U7.13 (SDA), U8.13 (SDA), U9.13 (SDA)
/VF1: J7.1, J7.2, J8.1, J8.2
/VF2: J7.5, J7.6, J8.5, J8.6
/VF3: J9.1, J9.2, J10.1, J10.2
/VF4: J9.5, J9.6, J10.5, J10.6
/VGG: J5.3, J6.3
/VPP: J5.1, J6.1
GND: C1.2, C2.2, C3.2, C4.2, C5.2, C6.2, C7.2, C8.2, C9.2, C10.2, D1.8 (GND), D1.9 (GND), D2.8 (GND), D2.9 (GND), D3.8 (GND), D3.9 (GND), D4.8 (GND), D4.9 (GND), D5.8 (GND), D5.9 (GND), D6.8 (GND), D6.9 (GND), D7.8 (GND), D7.9 (GND), D8.8 (GND), D8.9 (GND), D9.8 (GND), D9.9 (GND), D10.8 (GND), D10.9 (GND), D11.8 (GND), D11.9 (GND), D12.8 (GND), D12.9 (GND), D13.2 (A), D14.2 (A), D22.2 (A), J1.1, J2.1, J3.1, J4.1, J5.2, J5.4, J6.2, J6.4, J7.3, J7.4, J8.3, J8.4, J9.3, J9.4, J10.3, J10.4, J11.2, U1.10 (VSS), U1.15 (A0), U1.16 (A1), U1.17 (A2), U2.10 (VSS), U3.10 (VSS), U4.10 (VSS), U5.10 (VSS), U6.10 (VSS), U6.15 (A0), U6.16 (A1), U7.10 (VSS), U7.17 (A2), U8.10 (VSS), U8.16 (A1), U8.17 (A2), U9.10 (VSS), U9.15 (A0), U9.17 (A2)
VCC: C1.1, C2.1, C3.1, C4.1, C5.1, C6.1, C7.1, C8.1, C9.1, C10.1, D1.1 (VCC), D1.16 (VCC), D2.1 (VCC), D2.16 (VCC), D3.1 (VCC), D3.16 (VCC), D4.1 (VCC), D4.16 (VCC), D5.1 (VCC), D5.16 (VCC), D6.1 (VCC), D6.16 (VCC), D7.1 (VCC), D7.16 (VCC), D8.1 (VCC), D8.16 (VCC), D9.1 (VCC), D9.16 (VCC), D10.1 (VCC), D10.16 (VCC), D11.1 (VCC), D11.16 (VCC), D12.1 (VCC), D12.16 (VCC), D22.1 (K), J5.5, J5.6, J6.5, J6.6, R1.1, R4.1, R5.1, RN1.1 (common), RN2.1 (common), RN3.1 (common), RN4.1 (common), RN5.1 (common), RN6.1 (common), RN7.1 (common), RN8.1 (common), RN9.1 (common), RN10.1 (common), RN11.1 (common), RN12.1 (common), U1.9 (VDD), U2.9 (VDD), U3.9 (VDD), U4.9 (VDD), U5.9 (VDD), U6.9 (VDD), U7.9 (VDD), U8.9 (VDD), U9.9 (VDD)

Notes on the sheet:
SDA3.3
GND
SCK3.3

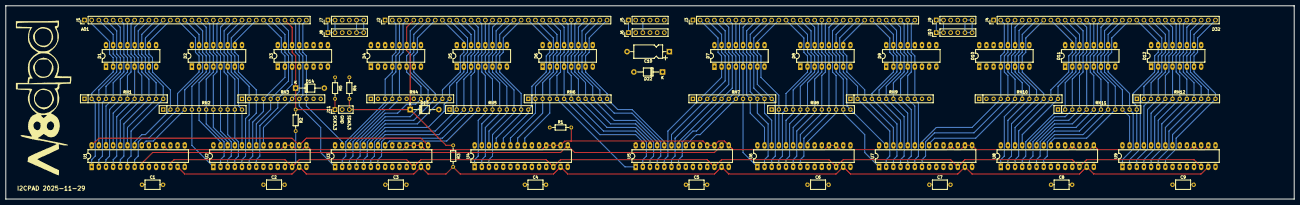
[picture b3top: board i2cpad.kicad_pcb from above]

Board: 4 copper layers, 457.2 x 68.6 mm, 62 parts (0 on the bottom side), 137 nets.
